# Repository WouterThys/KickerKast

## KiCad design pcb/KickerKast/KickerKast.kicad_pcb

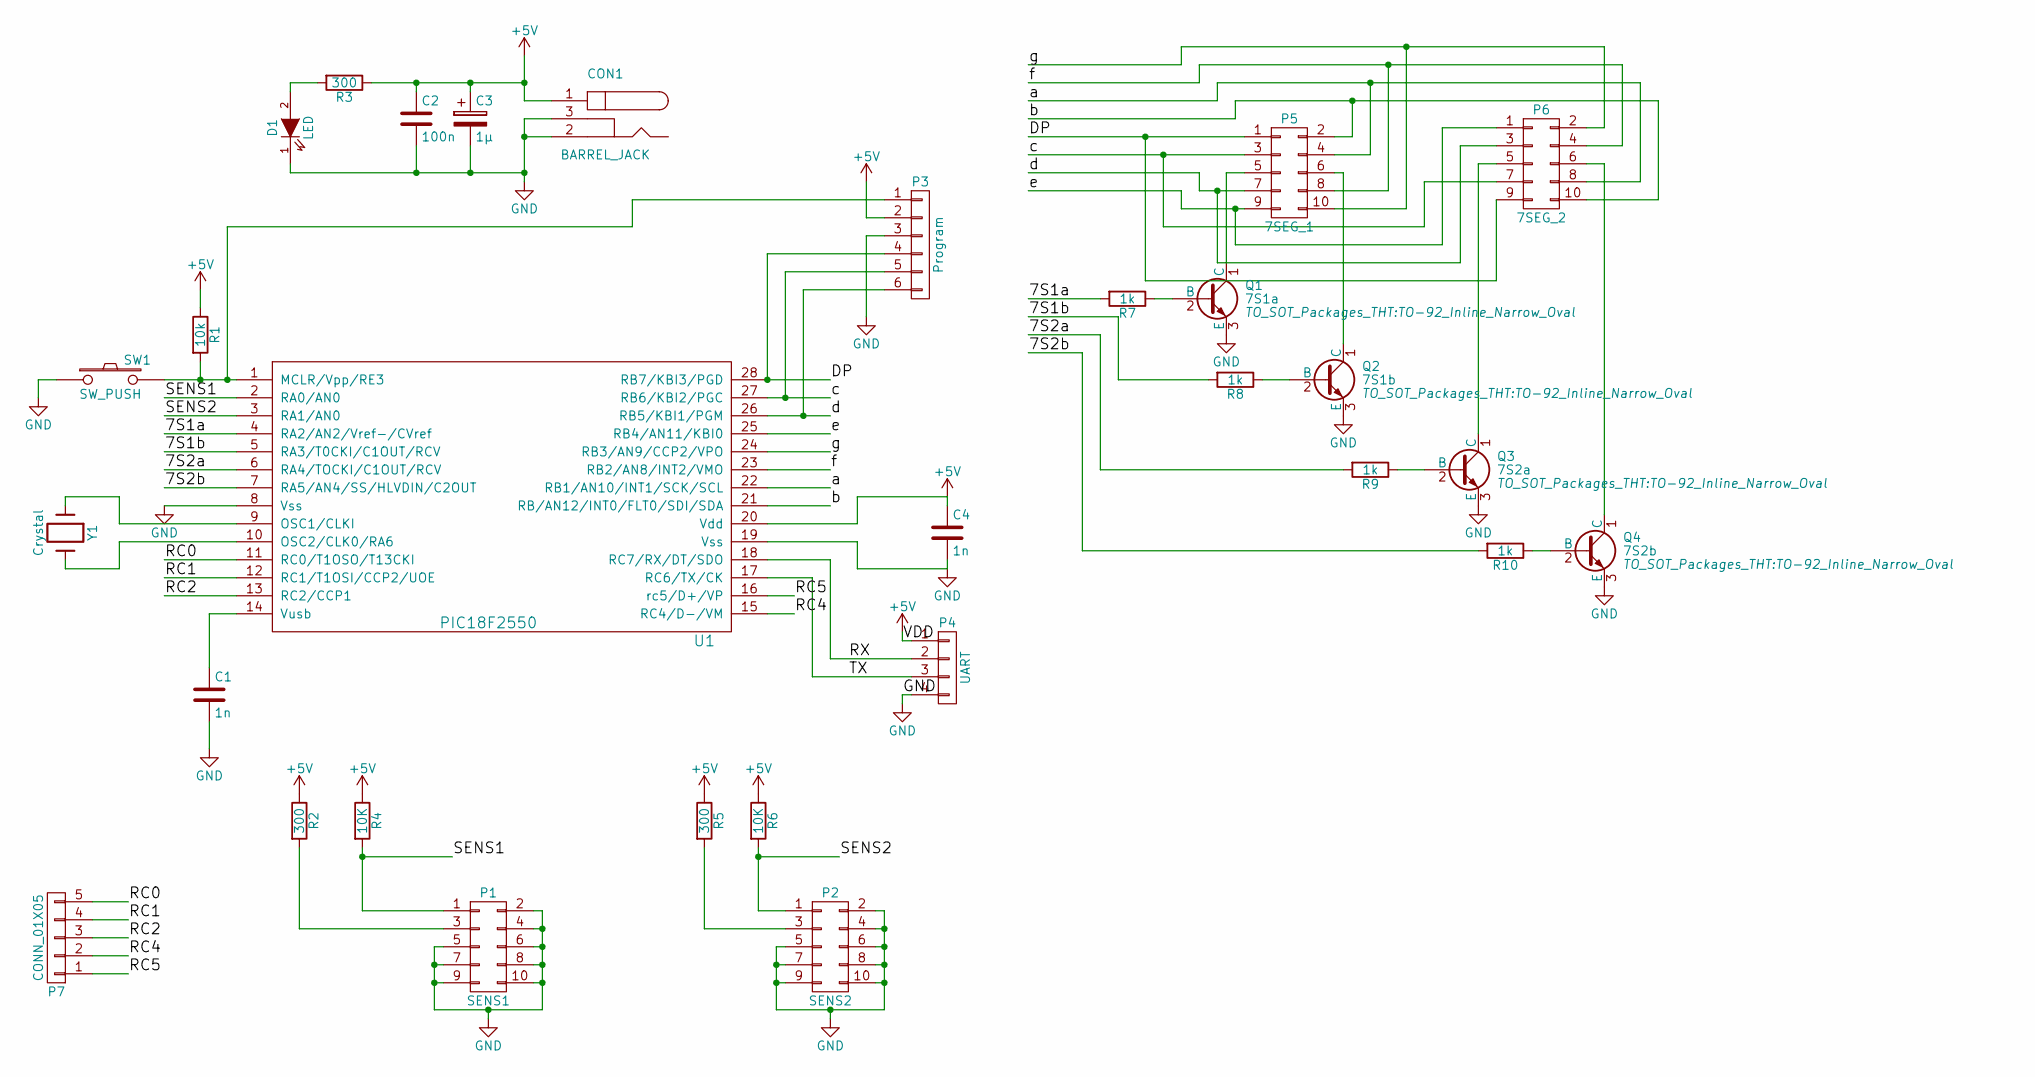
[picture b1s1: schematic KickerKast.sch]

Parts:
C1, C4: 1n; C_Disc_D3_P2.5
C2: 100n; C_Disc_D3_P2.5
C3: 1µ; C_Radial_D5_L6_P2.5
CON1: BARREL_JACK
D1: LED; LED-3MM
P1: SENS1; Pin_Header_Straight_2x05
P2: SENS2; Pin_Header_Straight_2x05
P3: Program; Pin_Header_Straight_1x06
P4: UART; Pin_Header_Straight_1x04
P5: 7SEG_1; Pin_Header_Straight_2x05
P6: 7SEG_2; Pin_Header_Straight_2x05
P7: CONN_01X05; Pin_Header_Straight_1x05
Q1: 7S1a; TO-92_Inline_Narrow_Oval
Q2: 7S1b; TO-92_Inline_Narrow_Oval
Q3: 7S2a; TO-92_Inline_Narrow_Oval
Q4: 7S2b; TO-92_Inline_Narrow_Oval
R1: 10k; Resistor_Horizontal_RM10mm
R2, R3, R5: 300; Resistor_Horizontal_RM10mm
R4, R6: 10K; Resistor_Horizontal_RM10mm
R7, R8, R9, R10: 1k; Resistor_Horizontal_RM10mm
SW1: SW_PUSH; SW_PUSH-12mm
U1: PIC18F2550; DIP-28_W7.62mm_LongPads
Y1: Crystal; Crystal_HC49-U_Vertical

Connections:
+5V: C2.1, C3.1, C4.1, CON1.1, P3.2, P4.1, R1.1, R2.1, R3.1, R4.1, R5.1, R6.1, U1.20 (Vdd)
/7S1a: R7.2, U1.4 (RA2/AN2/Vref-/CVref)
/7S1b: R8.2, U1.5 (RA3/T0CKI/C1OUT/RCV)
/7S2a: R9.2, U1.6 (RA4/TOCKI/C1OUT/RCV)
/7S2b: R10.2, U1.7 (RA5/AN4/SS/HLVDIN/C2OUT)
/DP: P3.4, P5.1, P6.9, U1.28 (RB7/KBI3/PGD)
/RC0: P7.5, U1.11 (RC0/T1OSO/T13CKI)
/RC1: P7.4, U1.12 (RC1/T1OSI/CCP2/UOE)
/RC2: P7.3, U1.13 (RC2/CCP1)
/RC4: P7.2, U1.15 (RC4/D-/VM)
/RC5: P7.1, U1.16 (rc5/D+/VP)
/RX: P4.2, U1.18 (RC7/RX/DT/SDO)
/SENS1: P1.1, R4.2, U1.2 (RA0/AN0)
/SENS2: P2.1, R6.2, U1.3 (RA1/AN0)
/TX: P4.3, U1.17 (RC6/TX/CK)
/a: P5.4, P6.8, U1.22 (RB1/AN10/INT1/SCK/SCL)
/b: P5.2, P6.10, U1.21 (RB/AN12/INT0/FLT0/SDI/SDA)
/c: P3.5, P5.3, P6.7, U1.27 (RB6/KBI2/PGC)
/d: P3.6, P5.7, P6.3, U1.26 (RB5/KBI1/PGM)
/e: P5.9, P6.1, U1.25 (RB4/AN11/KBI0)
/f: P5.8, P6.4, U1.23 (RB2/AN8/INT2/VMO)
/g: P5.10, P6.2, U1.24 (RB3/AN9/CCP2/VPO)
GND: C1.2, C2.2, C3.2, C4.2, CON1.2, CON1.3, D1.1 (K), P1.2, P1.4, P1.5, P1.6, P1.7, P1.8, P1.9, P1.10, P2.2, P2.4, P2.5, P2.6, P2.7, P2.8, P2.9, P2.10, P3.3, P4.4, Q1.3 (E), Q2.3 (E), Q3.3 (E), Q4.3 (E), SW1.1, U1.8 (Vss), U1.19 (Vss)
unnamed: C1.1, U1.14 (Vusb)
unnamed: D1.2 (A), R3.2
unnamed: P1.3, R2.2
unnamed: P2.3, R5.2
unnamed: P3.1, R1.2, SW1.2, U1.1 (MCLR/Vpp/RE3)
unnamed: P5.5, Q1.1 (C)
unnamed: P5.6, Q2.1 (C)
unnamed: P6.5, Q3.1 (C)
unnamed: P6.6, Q4.1 (C)
unnamed: Q1.2 (B), R7.1
unnamed: Q2.2 (B), R8.1
unnamed: Q3.2 (B), R9.1
unnamed: Q4.2 (B), R10.1
unnamed: U1.9 (OSC1/CLKI), Y1.1
unnamed: U1.10 (OSC2/CLK0/RA6), Y1.2

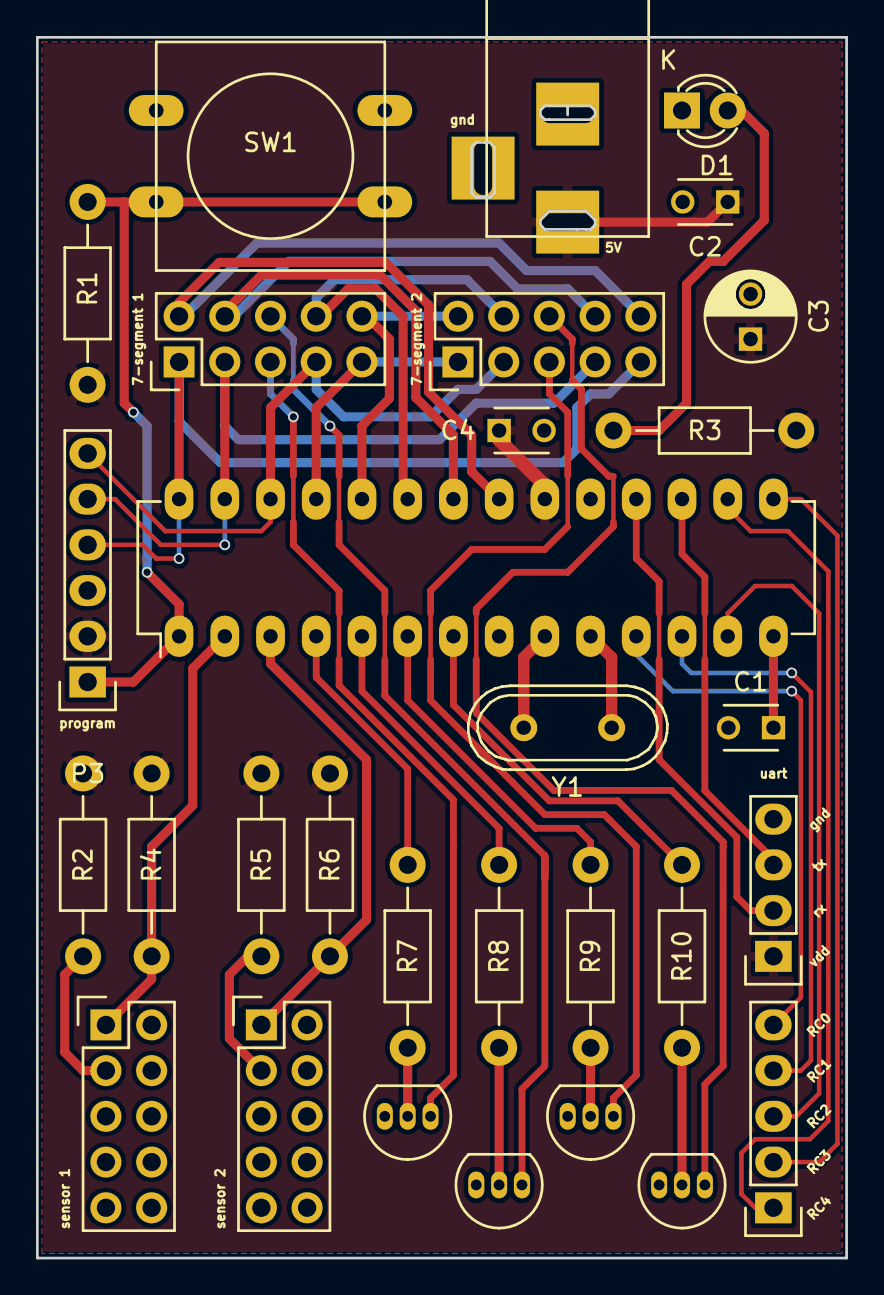
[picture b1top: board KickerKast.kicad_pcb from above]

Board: 2 copper layers, 45.0 x 67.8 mm, 30 parts (0 on the bottom side), 38 nets.

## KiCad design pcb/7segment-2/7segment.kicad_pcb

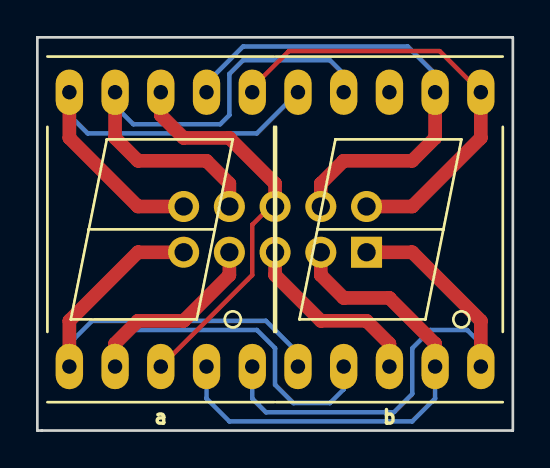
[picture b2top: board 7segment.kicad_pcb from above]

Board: 2 copper layers, 26.4 x 21.8 mm, 3 parts (1 on the bottom side), 10 nets.

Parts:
AFF1, AFF2: 7SEGMENTS; 7SegmentLED_LTS6760_LTS6780
P1: CONN_02X05; Pin_Header_Straight_2x05

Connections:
unnamed: AFF1.1, AFF2.1, P1.9
unnamed: AFF1.2, AFF2.2, P1.7
unnamed: AFF1.3, AFF1.8, P1.6
unnamed: AFF1.4, AFF2.4, P1.3
unnamed: AFF1.5, AFF2.5, P1.1
unnamed: AFF1.6, AFF2.6, P1.2
unnamed: AFF1.7, AFF2.7, P1.4
unnamed: AFF1.9, AFF2.9, P1.8
unnamed: AFF1.10, AFF2.10, P1.10
unnamed: AFF2.3, AFF2.8, P1.5

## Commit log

2016-10-22 added pcb files
2016-10-22 added pinout to 7-segment pcb
2016-10-22 added text to kickerkast pcb
2016-10-22 added extra connector to kickerkast pcb
2016-10-22 split 7-segment pcb text
2016-10-22 added extra drill to kickerkast pcb
2016-11-19 add some files
2016-11-19 added segment map file
2019-04-22 description
